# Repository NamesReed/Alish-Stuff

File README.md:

# Alish Design Files

It has been so long, I THINK these are the most up to date versions.

I do not remember if anything has changed between these files and final shipped products.

Print/cut/order parts for this at your own risk. Please verify files match your unit via actual measurements.

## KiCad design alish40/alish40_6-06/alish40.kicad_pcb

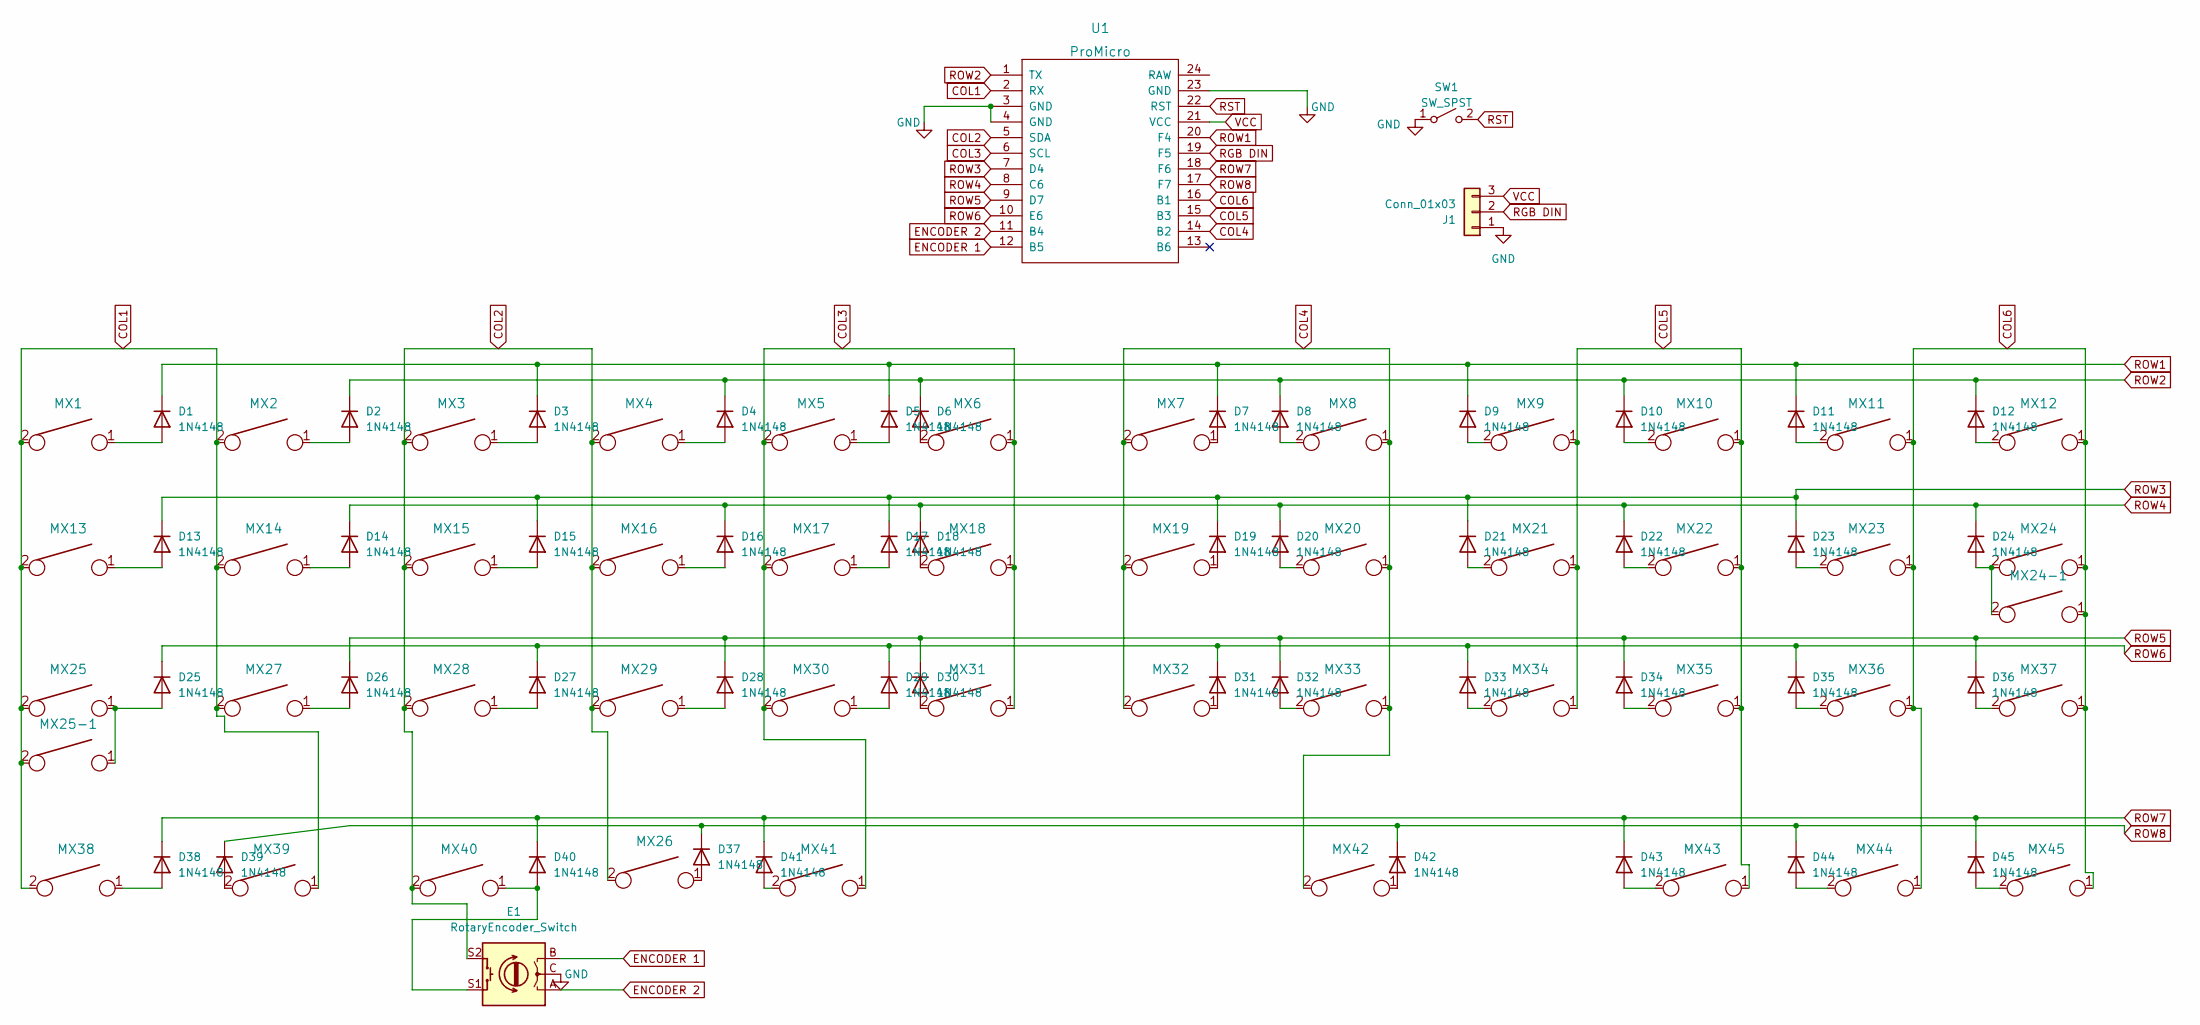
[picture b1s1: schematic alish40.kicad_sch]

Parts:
D1, D2, D3, D4, D5, D6, D7, D8, D9, D10, D11, D12, D13, D14, D15, D16, D17, D18, D19, D20, D21, D22, D23, D24, D25, D26, D27, D28, D29, D30, D31, D32, D33, D34, D35, D36, D37, D38, D39, D40, D41, D42, D43, D44, D45: 1N4148; clean_diode
E1: RotaryEncoder_Switch; RotaryEncoder_EC11
J1: Conn_01x03; PinHeader_1x03_P2.54mm_Vertical
MX1, MX2, MX3, MX4, MX5, MX6, MX7, MX8, MX9, MX10, MX11, MX12, MX13, MX14, MX15, MX16, MX17, MX18, MX19, MX20, MX21, MX22, MX23, MX24, MX24-1, MX25, MX25-1, MX26, MX27, MX28, MX29, MX30, MX31, MX32, MX33, MX34, MX35, MX36, MX37, MX38, MX39, MX40, MX41, MX42, MX43, MX44, MX45: KEYSW; SW_Cherry_MX_1.00u_PCB
SW1: SW_SPST; SW_PUSH_6mm
U1: ProMicro; Elite-C-castellated-24pin-holes

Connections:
COL1: MX1.2, MX2.2, MX13.2, MX14.2, MX25.2, MX25-1.2, MX27.2, MX38.2, MX39.1, U1.2 (RX)
COL2: E1.S2, MX3.2, MX4.2, MX15.2, MX16.2, MX26.2, MX28.2, MX29.2, MX40.2, U1.5 (SDA)
COL3: MX5.2, MX6.1, MX17.2, MX18.1, MX30.2, MX31.1, MX41.1, U1.6 (SCL)
COL4: MX7.2, MX8.1, MX19.2, MX20.1, MX32.2, MX33.1, MX42.2, U1.14 (B2)
COL5: MX9.1, MX10.1, MX21.1, MX22.1, MX34.1, MX35.1, MX43.1, U1.15 (B3)
COL6: MX11.1, MX12.1, MX23.1, MX24.1, MX24-1.1, MX36.1, MX37.1, MX44.1, MX45.1, U1.16 (B1)
ENCODER 1: E1.B, U1.12 (B5)
ENCODER 2: E1.A, U1.11 (B4)
GND: E1.C, J1.1, SW1.1 (A), U1.3 (GND), U1.4 (GND), U1.23 (GND)
unnamed: D1.2 (A), MX1.1
unnamed: D2.2 (A), MX2.1
unnamed: D3.2 (A), MX3.1
unnamed: D4.2 (A), MX4.1
unnamed: D5.2 (A), MX5.1
unnamed: D6.2 (A), MX6.2
unnamed: D7.2 (A), MX7.1
unnamed: D8.2 (A), MX8.2
unnamed: D9.2 (A), MX9.2
unnamed: D10.2 (A), MX10.2
unnamed: D11.2 (A), MX11.2
unnamed: D12.2 (A), MX12.2
unnamed: D13.2 (A), MX13.1
unnamed: D14.2 (A), MX14.1
unnamed: D15.2 (A), MX15.1
unnamed: D16.2 (A), MX16.1
unnamed: D17.2 (A), MX17.1
unnamed: D18.2 (A), MX18.2
unnamed: D19.2 (A), MX19.1
unnamed: D20.2 (A), MX20.2
unnamed: D21.2 (A), MX21.2
unnamed: D22.2 (A), MX22.2
unnamed: D23.2 (A), MX23.2
unnamed: D24.2 (A), MX24.2, MX24-1.2
unnamed: D25.2 (A), MX25.1, MX25-1.1
unnamed: D26.2 (A), MX27.1
unnamed: D27.2 (A), MX28.1
unnamed: D28.2 (A), MX29.1
unnamed: D29.2 (A), MX30.1
unnamed: D30.2 (A), MX31.2
unnamed: D31.2 (A), MX32.1
unnamed: D32.2 (A), MX33.2
unnamed: D33.2 (A), MX34.2
unnamed: D34.2 (A), MX35.2
unnamed: D35.2 (A), MX36.2
unnamed: D36.2 (A), MX37.2
unnamed: D38.2 (A), MX38.1
unnamed: D39.2 (A), MX39.2
unnamed: D40.2 (A), E1.S1, MX40.1
unnamed: D41.2 (A), MX41.2
unnamed: D42.2 (A), MX42.1
unnamed: D43.2 (A), MX43.2
unnamed: D44.2 (A), MX44.2
unnamed: D45.2 (A), MX45.2
unnamed: D37.2 (A), MX26.1
RGB DIN: J1.2, U1.19 (F5)
ROW1: D1.1 (K), D3.1 (K), D5.1 (K), D7.1 (K), D9.1 (K), D11.1 (K), U1.20 (F4)
ROW2: D2.1 (K), D4.1 (K), D6.1 (K), D8.1 (K), D10.1 (K), D12.1 (K), U1.1 (TX)
ROW3: D13.1 (K), D15.1 (K), D17.1 (K), D19.1 (K), D21.1 (K), D23.1 (K), U1.7 (D4)
ROW4: D14.1 (K), D16.1 (K), D18.1 (K), D20.1 (K), D22.1 (K), D24.1 (K), U1.8 (C6)
ROW5: D26.1 (K), D28.1 (K), D30.1 (K), D32.1 (K), D34.1 (K), D36.1 (K), U1.9 (D7)
ROW6: D25.1 (K), D27.1 (K), D29.1 (K), D31.1 (K), D33.1 (K), D35.1 (K), U1.10 (E6)
ROW7: D38.1 (K), D40.1 (K), D41.1 (K), D43.1 (K), D45.1 (K), U1.18 (F6)
ROW8: D37.1 (K), D39.1 (K), D42.1 (K), D44.1 (K), U1.17 (F7)
RST: SW1.2 (B), U1.22 (RST)
VCC: J1.3, U1.21 (VCC)

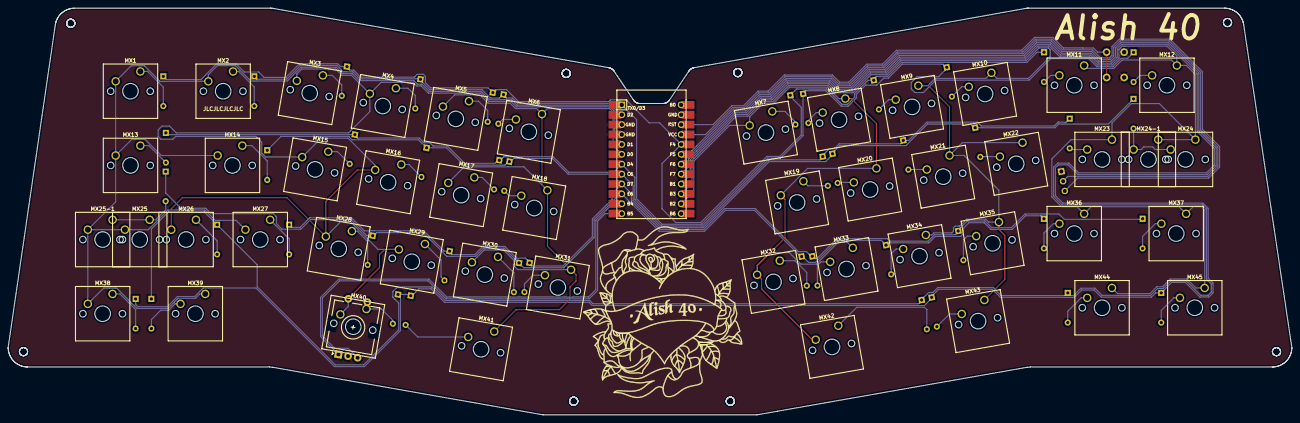
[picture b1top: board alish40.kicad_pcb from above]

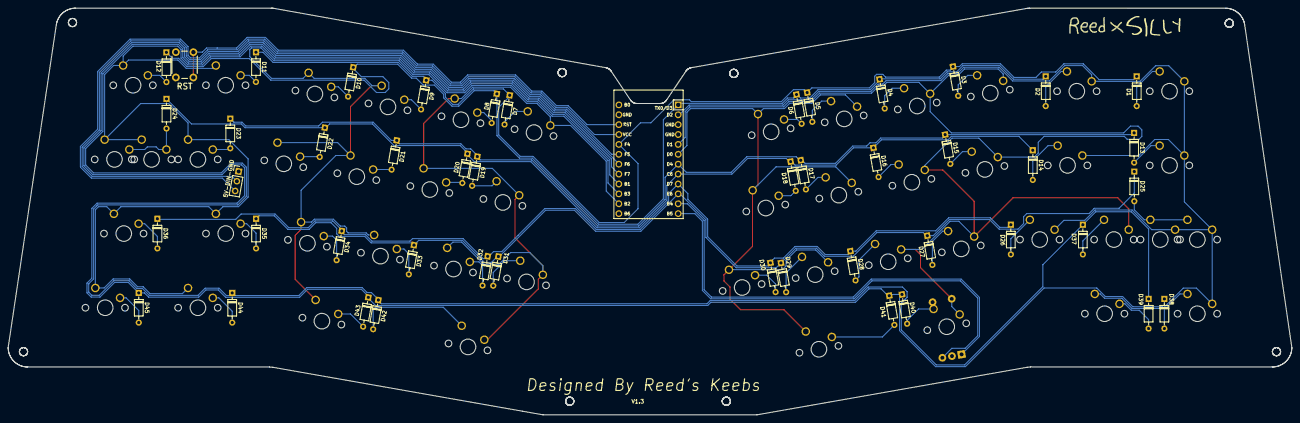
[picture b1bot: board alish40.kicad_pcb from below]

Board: 2 copper layers, 329.7 x 104.5 mm, 96 parts (47 on the bottom side), 65 nets.

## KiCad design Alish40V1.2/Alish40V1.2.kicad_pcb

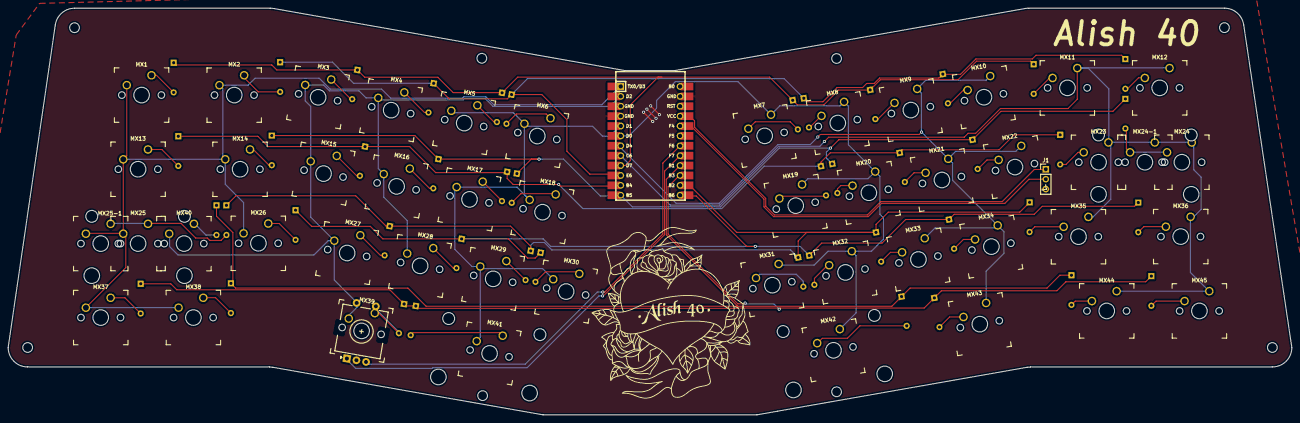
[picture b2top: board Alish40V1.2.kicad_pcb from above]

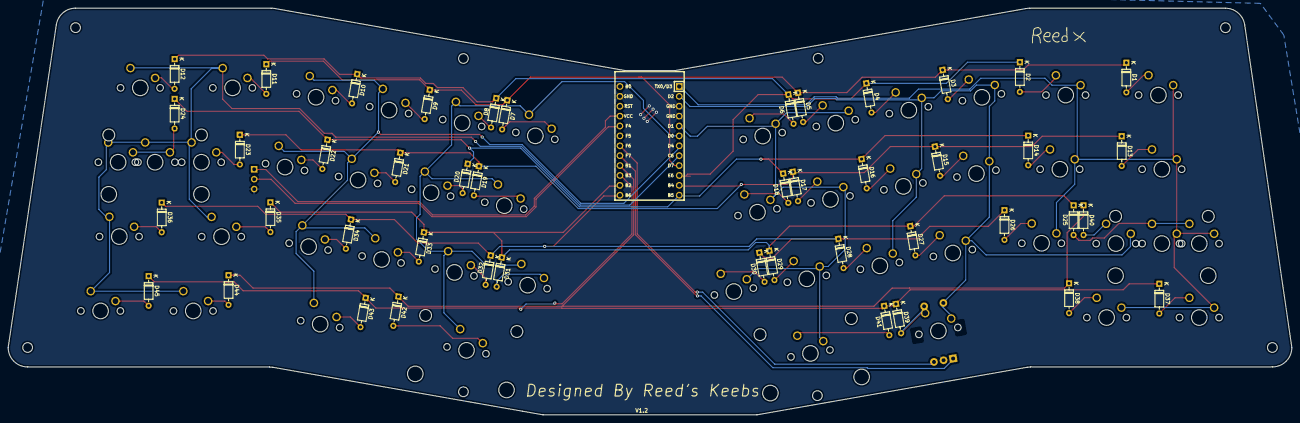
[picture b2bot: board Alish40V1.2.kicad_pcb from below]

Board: 2 copper layers, 329.7 x 104.5 mm, 95 parts (45 on the bottom side), 64 nets.

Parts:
D1, D2, D3, D4, D5, D6, D7, D8, D9, D10, D11, D12, D13, D14, D15, D16, D17, D18, D19, D20, D21, D22, D23, D24, D25, D26, D27, D28, D29, D30, D31, D32, D33, D34, D35, D36, D37, D38, D39, D40, D41, D42, D43, D44, D45: 1N4148; D_DO-35_SOD27_P7.62mm_Horizontal
E1: RotaryEncoder_Switch; RotaryEncoder_EC11
J1: Conn_01x03; PinHeader_1x03_P2.54mm_Vertical
MX1, MX12: KEYSW; 1.5U MX
MX2, MX3, MX4, MX5, MX6, MX7, MX8, MX9, MX10, MX11, MX14, MX15, MX16, MX17, MX18, MX19, MX20, MX21, MX22, MX23, MX26, MX27, MX28, MX29, MX30, MX31, MX32, MX33, MX34, MX35, MX40: KEYSW; 1U MX
MX13, MX36: KEYSW; 1.75U MX
MX24, MX25-1, MX37, MX38, MX39, MX43, MX44, MX45: KEYSW; 1.25U MX
MX24-1, MX25, MX41: KEYSW; 2.25U MX
MX42: KEYSW; SW_Cherry_MX_2.75u_PCB
U1: ProMicro; Elite-C-castellated-24pin-holes

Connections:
COL1: MX1.2, MX2.2, MX13.2, MX14.2, MX25.2, MX25-1.2, MX26.2, MX37.2, MX38.2, U1.1 (TX)
COL2: E1.S2, MX3.2, MX4.2, MX15.2, MX16.2, MX27.2, MX28.2, MX39.2, MX40.2, U1.2 (RX)
COL3: MX5.2, MX6.2, MX17.2, MX18.2, MX29.2, MX30.2, MX41.2, U1.5 (SDA)
COL4: MX7.1, MX8.1, MX19.1, MX20.1, MX31.1, MX32.1, MX42.1, U1.6 (SCL)
COL5: MX9.1, MX10.1, MX21.1, MX22.1, MX33.1, MX34.1, MX43.1, U1.7 (D4)
COL6: MX11.1, MX12.1, MX23.1, MX24.1, MX24-1.1, MX35.1, MX36.1, MX44.1, MX45.1, U1.8 (C6)
ENCODER 1: E1.B, U1.18 (F6)
ENCODER 2: E1.A, U1.17 (F7)
GND: E1.C, J1.3, U1.3 (GND), U1.4 (GND), U1.23 (GND)
unnamed: D1.2 (A), MX1.1
unnamed: D2.2 (A), MX2.1
unnamed: D3.2 (A), MX3.1
unnamed: D4.2 (A), MX4.1
unnamed: D5.2 (A), MX5.1
unnamed: D6.2 (A), MX6.1
unnamed: D7.2 (A), MX7.2
unnamed: D8.2 (A), MX8.2
unnamed: D9.2 (A), MX9.2
unnamed: D10.2 (A), MX10.2
unnamed: D11.2 (A), MX11.2
unnamed: D12.2 (A), MX12.2
unnamed: D13.2 (A), MX13.1
unnamed: D14.2 (A), MX14.1
unnamed: D15.2 (A), MX15.1
unnamed: D16.2 (A), MX16.1
unnamed: D17.2 (A), MX17.1
unnamed: D18.2 (A), MX18.1
unnamed: D19.2 (A), MX19.2
unnamed: D20.2 (A), MX20.2
unnamed: D21.2 (A), MX21.2
unnamed: D22.2 (A), MX22.2
unnamed: D23.2 (A), MX23.2
unnamed: D24.2 (A), MX24.2, MX24-1.2
unnamed: D25.2 (A), MX25.1, MX25-1.1
unnamed: D26.2 (A), MX26.1
unnamed: D27.2 (A), MX27.1
unnamed: D28.2 (A), MX28.1
unnamed: D29.2 (A), MX29.1
unnamed: D30.2 (A), MX30.1
unnamed: D31.2 (A), MX31.2
unnamed: D32.2 (A), MX32.2
unnamed: D33.2 (A), MX33.2
unnamed: D34.2 (A), MX34.2
unnamed: D35.2 (A), MX35.2
unnamed: D36.2 (A), MX36.2
unnamed: D37.2 (A), MX37.1
unnamed: D38.2 (A), MX38.1
unnamed: D39.2 (A), E1.S1, MX39.1
unnamed: D40.2 (A), MX40.1
unnamed: D41.2 (A), MX41.1
unnamed: D42.2 (A), MX42.2
unnamed: D43.2 (A), MX43.2
unnamed: D44.2 (A), MX44.2
unnamed: D45.2 (A), MX45.2
RGB DIN: J1.2, U1.20 (F4)
ROW1: D1.1 (K), D3.1 (K), D5.1 (K), D7.1 (K), D9.1 (K), D11.1 (K), U1.9 (D7)
ROW2: D2.1 (K), D4.1 (K), D6.1 (K), D8.1 (K), D10.1 (K), D12.1 (K), U1.10 (E6)
ROW3: D13.1 (K), D15.1 (K), D17.1 (K), D19.1 (K), D21.1 (K), D23.1 (K), U1.11 (B4)
ROW4: D14.1 (K), D16.1 (K), D18.1 (K), D20.1 (K), D22.1 (K), D24.1 (K), U1.12 (B5)
ROW5: D26.1 (K), D28.1 (K), D30.1 (K), D32.1 (K), D34.1 (K), D36.1 (K), U1.13 (B6)
ROW6: D25.1 (K), D27.1 (K), D29.1 (K), D31.1 (K), D33.1 (K), D35.1 (K), U1.14 (B2)
ROW7: D37.1 (K), D39.1 (K), D41.1 (K), D43.1 (K), D45.1 (K), U1.15 (B3)
ROW8: D38.1 (K), D40.1 (K), D42.1 (K), D44.1 (K), U1.16 (B1)
VCC: J1.1, U1.21 (VCC)

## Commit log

2022-04-15 Uploaded Alish40 Files
2022-04-16 Updated all files
    New artwork, fixed traces and footprints on wrong side of board, included backplate
2022-04-21 Updated PCB and Schematic
    Changed Reference Designators, updated footprints, fixed several routing issues, added Reed X (silly), added my footprints, moved encoder slightly, tightened up QAZ to WSX spacing.
2022-06-16 Update board, remove un-needed files
2022-06-16 this is everything <3
2022-06-16 added art
2022-06-16 redo everything lmao
2022-07-17 New PCB file rerouted by silly. Needs silkscreen cleaned up, header info on schematic, incremented versioning on PCB silkscreen, JLCJLCJLCJLC on PCB silkscreen, remove k notation on the diodes (I rec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
2022-07-20 converted to be backwards compatible with kicad 6.06
2022-07-20 final proto finished
2022-07-20 syncing updated rhino file
2022-12-13 Fix 1u switch error
2022-12-14 modified traces to not be under drill holes
